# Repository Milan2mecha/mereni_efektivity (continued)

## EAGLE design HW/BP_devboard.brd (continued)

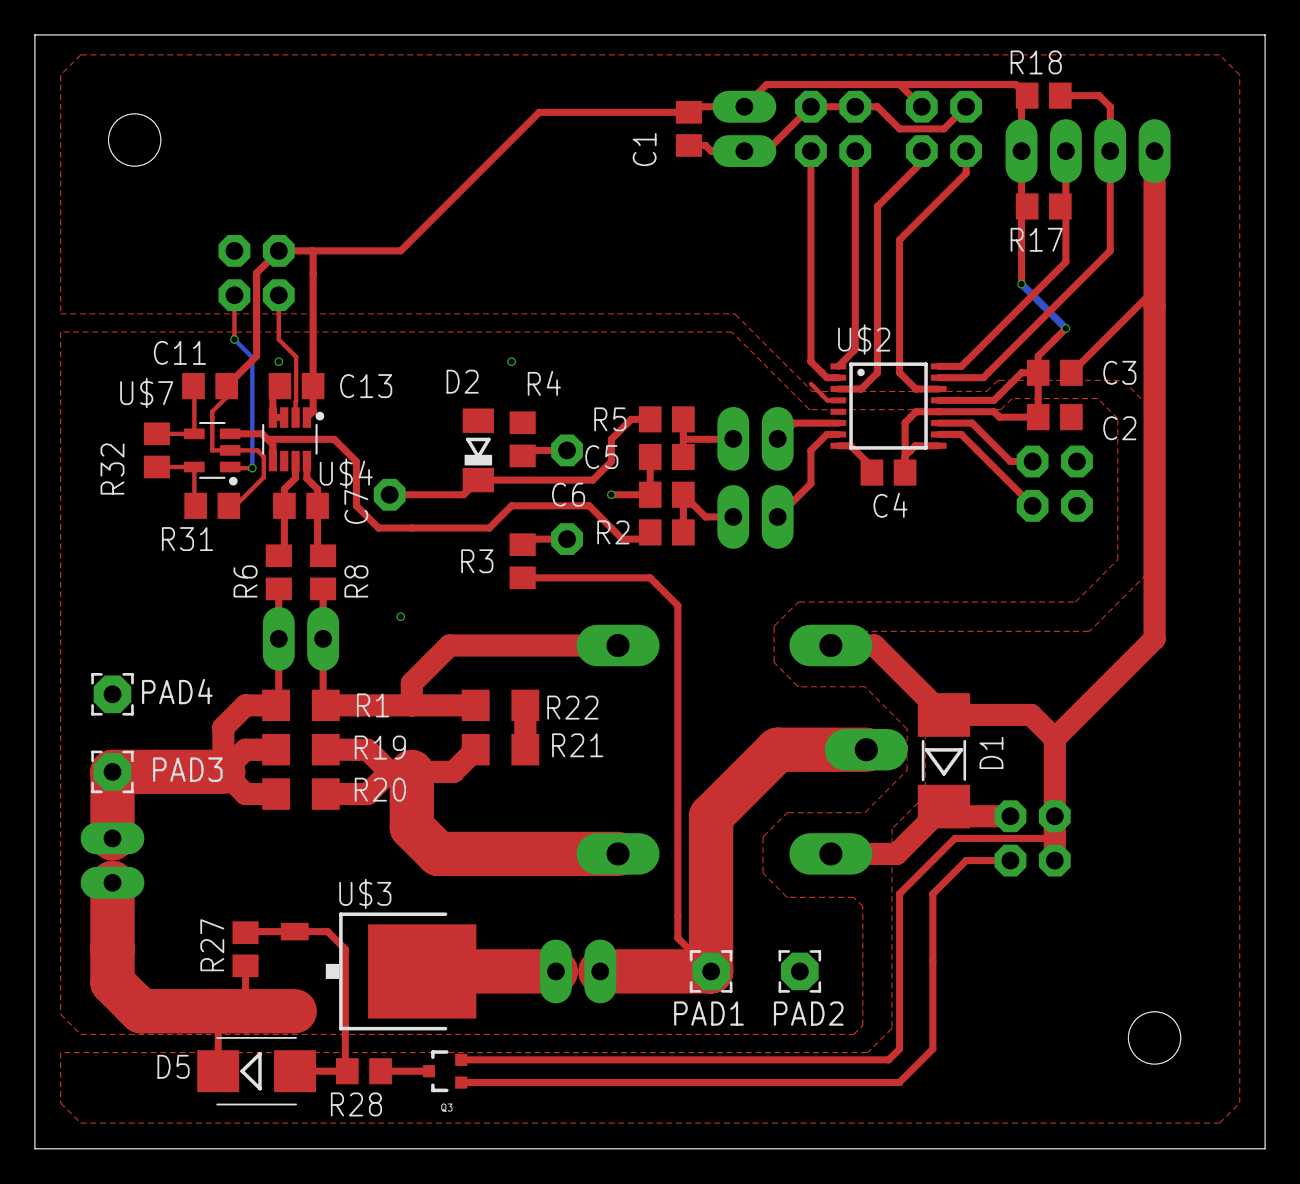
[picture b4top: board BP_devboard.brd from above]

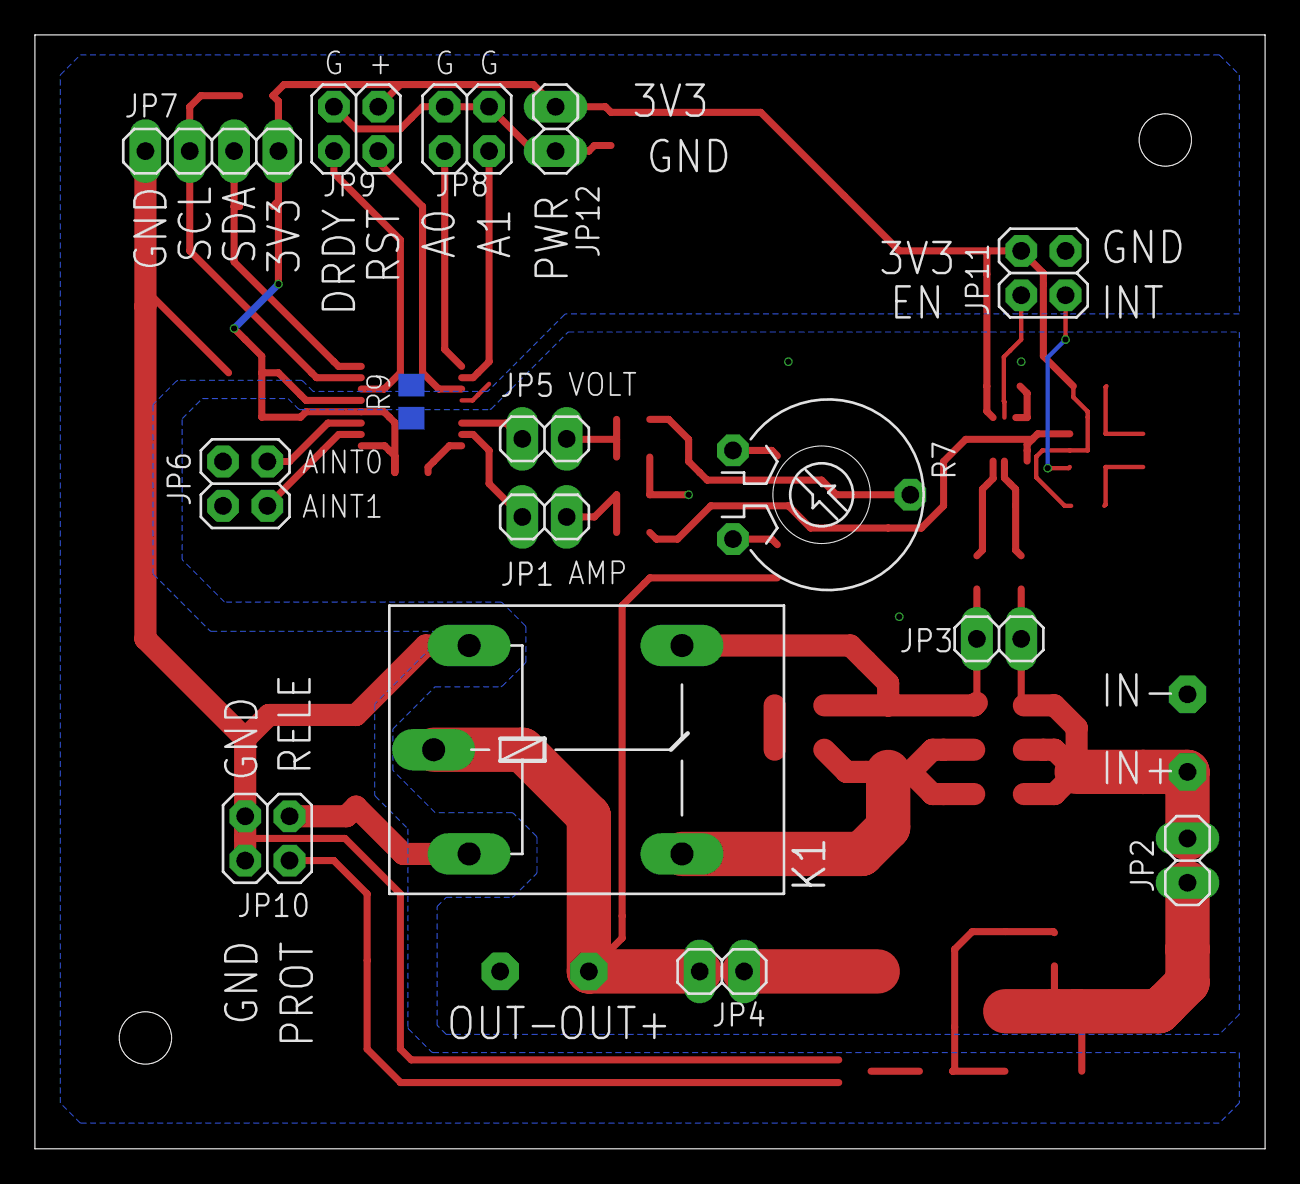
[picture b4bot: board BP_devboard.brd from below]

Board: 2 copper layers, 70.5 x 63.8 mm, 53 parts (15 on the bottom side), 35 nets.

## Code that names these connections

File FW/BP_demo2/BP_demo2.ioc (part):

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Mcu.Name=STM32F103C(8-B)Tx
Mcu.Package=LQFP48
Mcu.UserName=STM32F103C8Tx
PA11.Mode=Device
PA11.Signal=USB_DM
PA12.Mode=Device
PA12.Signal=USB_DP
PA3.Signal=GPIO_Input
PA4.Signal=GPIO_Output
PA5.Signal=GPIO_Input
PA6.Signal=GPIO_Output
PB0.Signal=GPXTI0
PB1.Signal=GPXTI1
PB12.Signal=GPIO_Output
PB13.Signal=GPIO_Output
PB14.Signal=GPIO_Output
PB15.Signal=GPIO_Output
PB6.Mode=I2C
PB6.Signal=I2C1_SCL
PB7.Mode=I2C
PB7.Signal=I2C1_SDA
PD0-OSC_IN.Mode=HSE-External-Oscillator
PD0-OSC_IN.Signal=RCC_OSC_IN
PD1-OSC_OUT.Mode=HSE-External-Oscillator
PD1-OSC_OUT.Signal=RCC_OSC_OUT
RCC.SYSCLKFreq_VALUE=72000000
RCC.SYSCLKSource=RCC_SYSCLKSOURCE_PLLCLK
board=custom

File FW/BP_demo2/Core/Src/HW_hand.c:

#include "gpio.h"
#include "i2c.h"
#include "ADS121X.h"
#include "HW_hand.h"
#include "tim.h"

#define PROT1 GPIOB,GPIO_PIN_12
#define PROT2 GPIOB,GPIO_PIN_14
#define STAV_IN GPIOA,GPIO_PIN_3
#define STAV_OUT GPIOA,GPIO_PIN_5
#define RIZENI_IN GPIOA,GPIO_PIN_4
#define RIZENI_OUT GPIOA,GPIO_PIN_6
#define RELE1 GPIOB,GPIO_PIN_13
#define RELE2 GPIOB,GPIO_PIN_15

const float CurrKoef[2][2][3] = {{{0,1,0},{0,1,0}},{{0,1,0},{0,1,0}}}; //rozsah5A, rozsah1A -> absolutní,lineární,kvadratický
const float VoltKoef[2][3] = {{0,1,0},{0,1,0}}; //absolutní,lineární,kvadratický

uint8_t range[]={1,1}; //0=5A,1=1A
uint8_t rangeOVF[]={0,0};//přetečení rozsahu

void Delay_TIM(uint16_t time){
	time *= 40;
	uint16_t start = __HAL_TIM_GET_COUNTER(&htim1);
	while(__HAL_TIM_GET_COUNTER(&htim1)!=((start+time)%10000)){
		__NOP();
	}
}
/*Provizorní řešení, vyhledově snaha nahradit*/
void delay_loop(volatile uint32_t count) {
    while (count--) {
        __NOP();  // No Operation (zabrání odstranění smyčky optimalizátorem)
    }
}

void HAL_GPIO_EXTI_Callback(uint16_t GPIO_Pin){
	if(GPIO_Pin == GPIO_PIN_0){
        if(HAL_GPIO_ReadPin(RIZENI_IN)){
            if(range[0]){
                HAL_GPIO_WritePin(PROT1,1);
                range[0]=0;
                HAL_GPIO_WritePin(RELE1,0);
                //HAL_Delay(10);//10ms rychlost sepnutí relé
                Delay_TIM(10);
                //delay_loop(240000);
                HAL_GPIO_WritePin(PROT1,0);
                return;
            }else{
                HAL_GPIO_WritePin(PROT1,1);
                rangeOVF[0]=1;
                return;
            }
        }else{
            return;
        }
	}
    if(GPIO_Pin == GPIO_PIN_1){
        if(HAL_GPIO_ReadPin(RIZENI_OUT)){
            if(range[1]){
                //Je na 1A rozsahu, přepíná na 5A
                HAL_GPIO_WritePin(PROT2,1);
                HAL_GPIO_WritePin(RELE2,0);
                range[1]=0;
                delay_loop(1000000);
               // HAL_Delay(10);//10ms rychlost sepnutí relé
                HAL_GPIO_WritePin(PROT2,0);
                return;
            }else{
                //Je na 5A rozsahu, přezkratuje zapíše registr
                HAL_GPIO_WritePin(PROT2,1);
                rangeOVF[1]=1;
                return;
            }
        }else{
            //kanál je vypnutý, ochrana nereaguje
            return;
        }
	}
}

uint8_t HW_range(uint8_t channel)
{
	return range[channel];
}

uint8_t HW_status(void){
    if(HAL_GPIO_ReadPin(STAV_IN) == 0){
        HAL_GPIO_WritePin(RIZENI_IN, 0);
        return 1;
    }
    if(HAL_GPIO_ReadPin(STAV_OUT) == 0){
        HAL_GPIO_WritePin(RIZENI_OUT, 0);
        return 1;
    }
    if((rangeOVF[0]==1) || (rangeOVF[0]==1)){
        return 2;
    }
    return 0;
}

uint8_t HW_init(void){
    //Nastaví rozsah
    HAL_GPIO_WritePin(RELE1, range[0]);
    HAL_GPIO_WritePin(RELE2, range[1]);
    //reset PROT
    HAL_GPIO_WritePin(PROT1, 1);
    HAL_GPIO_WritePin(PROT2, 1);
    HAL_Delay(10);
    HAL_GPIO_WritePin(PROT1, 0);
    HAL_GPIO_WritePin(PROT2, 0);
   // ADS121X_init();
   // ADS121X_cal();
    return 0;
}

int8_t HW_switch(uint8_t channel, int8_t status){
    if(channel == 1){
        if(HAL_GPIO_ReadPin(STAV_IN) == 1){
            HAL_GPIO_WritePin(RIZENI_IN, status);
            return 1;
        }else{
            HAL_GPIO_WritePin(RIZENI_IN, 0);
            return -1;
        }
    }
    else if(channel == 2){
        if(HAL_GPIO_ReadPin(STAV_IN) == 1){
            HAL_GPIO_WritePin(RIZENI_IN, status);
            return 1;
        }else{
            HAL_GPIO_WritePin(RIZENI_IN, 0);
            return -1;
        }
    }
    else{
        return -1;
    }
}


float HW_voltage(uint8_t channel){
    ADS121X_MUX((channel*2)+1, AGND);
    float tmp = ADS121X_Voltage(ADS121X_meas_sg(), 0, 0);
    float out = (tmp*tmp*VoltKoef[channel][2])+(tmp*VoltKoef[channel][1])+VoltKoef[channel][0];
    return out;
}

float HW_current(uint8_t channel){
    ADS121X_MUX((channel*2), AGND);
    float tmp = ADS121X_Voltage(ADS121X_meas_sg(), 0, 0);
    float out = (tmp*tmp*CurrKoef[channel][range[channel]][2])+(tmp*CurrKoef[channel][range[channel]][1])+CurrKoef[channel][range[channel]][0];
    return out;
}

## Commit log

2024-09-21 Vytvoření knihovny pro ADS111X
2024-09-22 Vytvoření ADS121X
2024-10-13 Vytvoření schémat analogové a digitální části.
2024-10-19 Úvodní návrh devboardu a návrh obvodů pro detekci přepolování a přepětí
2024-10-26 Simulace okénkového komparátoru pro ochrannou desku
2024-10-27 Návrh desky ochran
2024-10-29 Přidáno propojení desek fastony a distančními sloupky, změněna logika vyhodnocení nežádoucích stavů
2024-11-03 Oprava knihovny pro ADC
2024-11-10 Vytvoření ovládací desky, simulace a úprava filtrů
2024-11-15 Oprava označení
2024-11-16 Přepracování inicializačních funkcí, odstranění bugů a zanechání práce na knihovně ADS111X
2024-11-17 Přidán přepočet na napětí, menší změny v dokumentaci
2024-12-08 Verze zadaná do výroby
2025-02-08 Přidání kostry FW v modifikaci pro provoz v konzoli
2025-02-16 Vytvořemí demonstračního programu funkce HW, základní verze
2025-02-23 Přidání demo programů pro zobrazování na OLED a pro simulaci NI LabView
2025-02-27 Oprava PC_PC demo
2025-02-28 Oprava návratu doublepracidion hodnot v USB demo (bez použití snprintf), optimalizace
2025-02-28 Vytviřena kompatibilita mezi demo_US a demo_PC-PC
2025-03-01 Zahájení prací na driveru pro LabView
2025-03-01 Funkce MEAS a SYS:MODE
2025-03-02 Přetaktování MCU v USB-demo
2025-03-04 Přepis měřicích funkcí DMM do struct
2025-03-06 Přepsání na structy
2025-03-07 Autorange
2025-03-09 Automatické přepínání rozsahů s delayem přes TIM1
2025-03-14 demo na F103CB s funkčním autorangem
2025-03-14 Oprava HW_hand do funční podoby
2025-03-15 Verze dema se základní funkčností přes USB
2025-03-16 Základní funkčnosti VISA, odstranění starého dema
2025-03-19 přidání state machine
2025-03-19 Přepsání měření do statemachine, data s demo prvky
2025-03-22 Funkční přepínání range dolů
2025-03-23 Prodloužení přepínacích dob pro zvýšení stability
2025-03-26 Přidání profi zátěže do VI DEMO
2025-03-28 Přidání profi DMM a zdroje do ověřovacích VI
2025-03-29 Integrace DMM do V testu
2025-03-29 Přidání VI pro prodový test
2025-03-30 Neotestované přidané funkce FW
2025-04-04 Funkční verze FW s indexováním kanálů le normy SCPI
2025-04-06 Přidání a otestování subsystému FETCh a SRATe
2025-04-06 Odstranění starého dema
2025-04-15 Neotestované úpravy FW (přidání EEPROM)
2025-04-15 Zpřehlednění kódu
2025-04-16 Upravy kalibrace
2025-04-17 Příprava vi kalibrace
2025-04-17 Schéma desky MCU
2025-04-21 Opraveny funkce EEPROM, stále bez continous samplingu
2025-04-21 Opravy couborů HW deffinic
2025-04-21 Funkční BTESt subsystém
2025-04-21 Drobné úpravy v kódu pro doladění, nefunguje přerušení výstupního kanálu
2025-04-24 Drobné změny VI
2025-04-26 Vytvoření měřicího m´du pro DCIR
2025-04-27 Odstanění složky staré struktury
2025-04-27 Měření efektivity
2025-04-27 Dodaná energie (je třeba doladit přepínání rozsahů dolů)
2025-04-27 Přidání knihovny pro vlastní zátěž
2025-04-30 Přidání výsledků kalibračních měření
2025-05-04 Odstranění redundantních souborů
2025-05-10 Nové měřicí módy a drobná zlepšení
2025-05-11 Úpravy LabVIEW
2025-05-14 Měření rozptylu 1A
2025-05-16 Opravena chyba FW + zpřehlednění
2025-05-16 Instrument driver obrázky
